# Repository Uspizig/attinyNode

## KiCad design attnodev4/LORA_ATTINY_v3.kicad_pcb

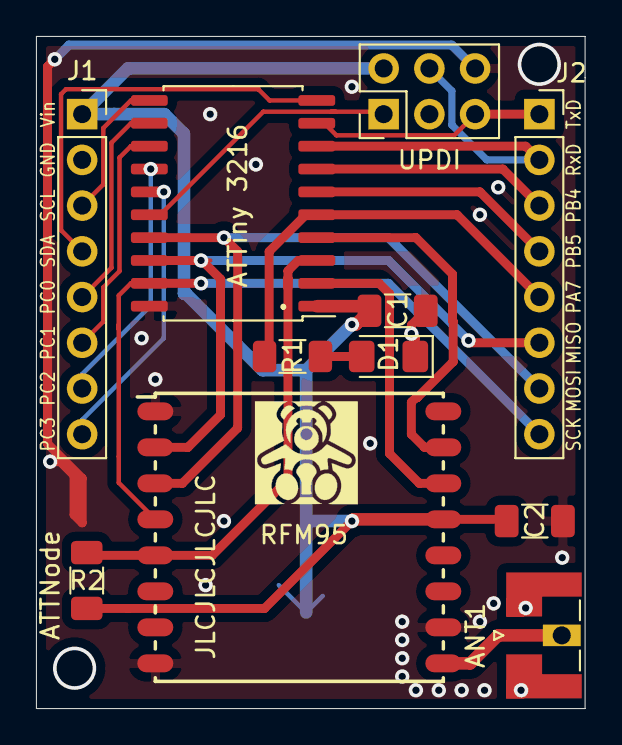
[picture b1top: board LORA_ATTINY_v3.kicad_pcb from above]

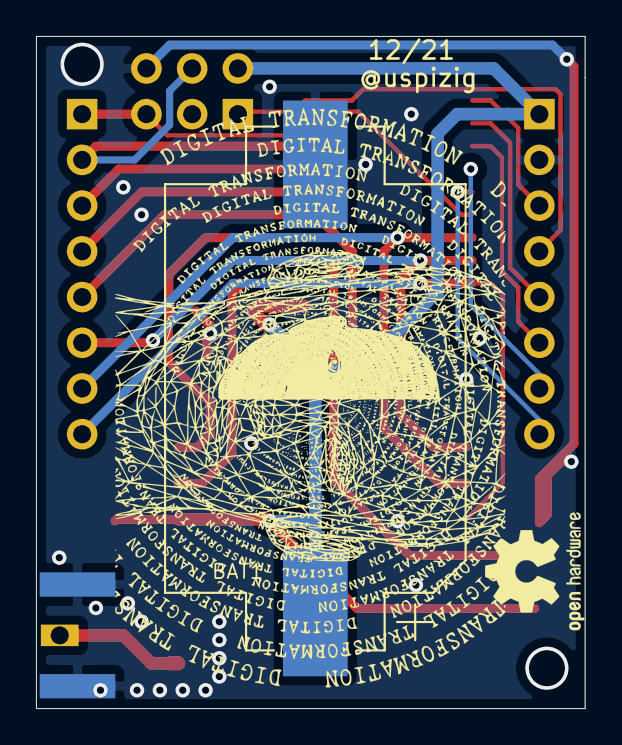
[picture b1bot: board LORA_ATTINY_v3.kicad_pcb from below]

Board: 2 copper layers, 30.5 x 37.3 mm, 13 parts (2 on the bottom side), 22 nets.

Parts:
ANT1: Antenna; SMA_Edge_UFL_Combo
ATTiny 3216: ATtiny3216-S; SOIC-20W_7.5x12.8mm_P1.27mm
BAT1: Battery_Cell; BatteryHolder_Keystone_1060_1x2032_Long_Pad
C1, C2: 100n; C_1206_3216Metric_Pad1.33x1.80mm_HandSolder
D1: LED; LED_1206_3216Metric_Pad1.42x1.75mm_HandSolder
J1, J2: Conn_01x08_Male; PinSocket_1x08_P2.54mm_Vertical
OSHW: OSHW-Logo2_7.3x6mm_SilkScreen
R1: 100; R_1206_3216Metric_Pad1.30x1.75mm_HandSolder
R2: 47K; R_1206_3216Metric_Pad1.30x1.75mm_HandSolder
RFM95: RFM95W-868S2; RFM95
UPDI: PRG; PinHeader_2x03_P2.54mm_Vertical

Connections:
+3V3: ATTiny 3216.1, BAT1.1, C1.1, C2.1, J1.1, R2.2, RFM95.13, UPDI.2
DIO0: ATTiny 3216.2, RFM95.14
DIO1: ATTiny 3216.4, RFM95.15
GND: ANT1.2, ATTiny 3216.20, BAT1.2, C1.2, C2.2, D1.1, J1.2, RFM95.1, RFM95.8, RFM95.10, UPDI.6
MISO: ATTiny 3216.18, J2.6, RFM95.2
MOSI: ATTiny 3216.17, J2.7, RFM95.3
NSS: ATTiny 3216.3, R2.1, RFM95.5
unnamed: ANT1.1, RFM95.9
unnamed: D1.2, R1.1
PA7: ATTiny 3216.5, J2.5, R1.2
PB0: ATTiny 3216.11, J1.3
PB1: ATTiny 3216.10, J1.4
PB2: ATTiny 3216.9, J2.1, UPDI.5
PB3: ATTiny 3216.8, J2.2, UPDI.4
PB4: ATTiny 3216.7, J2.3
PB5: ATTiny 3216.6, J2.4
PC0: ATTiny 3216.12, J1.5
PC1: ATTiny 3216.13, J1.6
PC2: ATTiny 3216.14, J1.7
PC3: ATTiny 3216.15, J1.8
RST: ATTiny 3216.16, UPDI.1
SCK: ATTiny 3216.19, J2.8, RFM95.4
